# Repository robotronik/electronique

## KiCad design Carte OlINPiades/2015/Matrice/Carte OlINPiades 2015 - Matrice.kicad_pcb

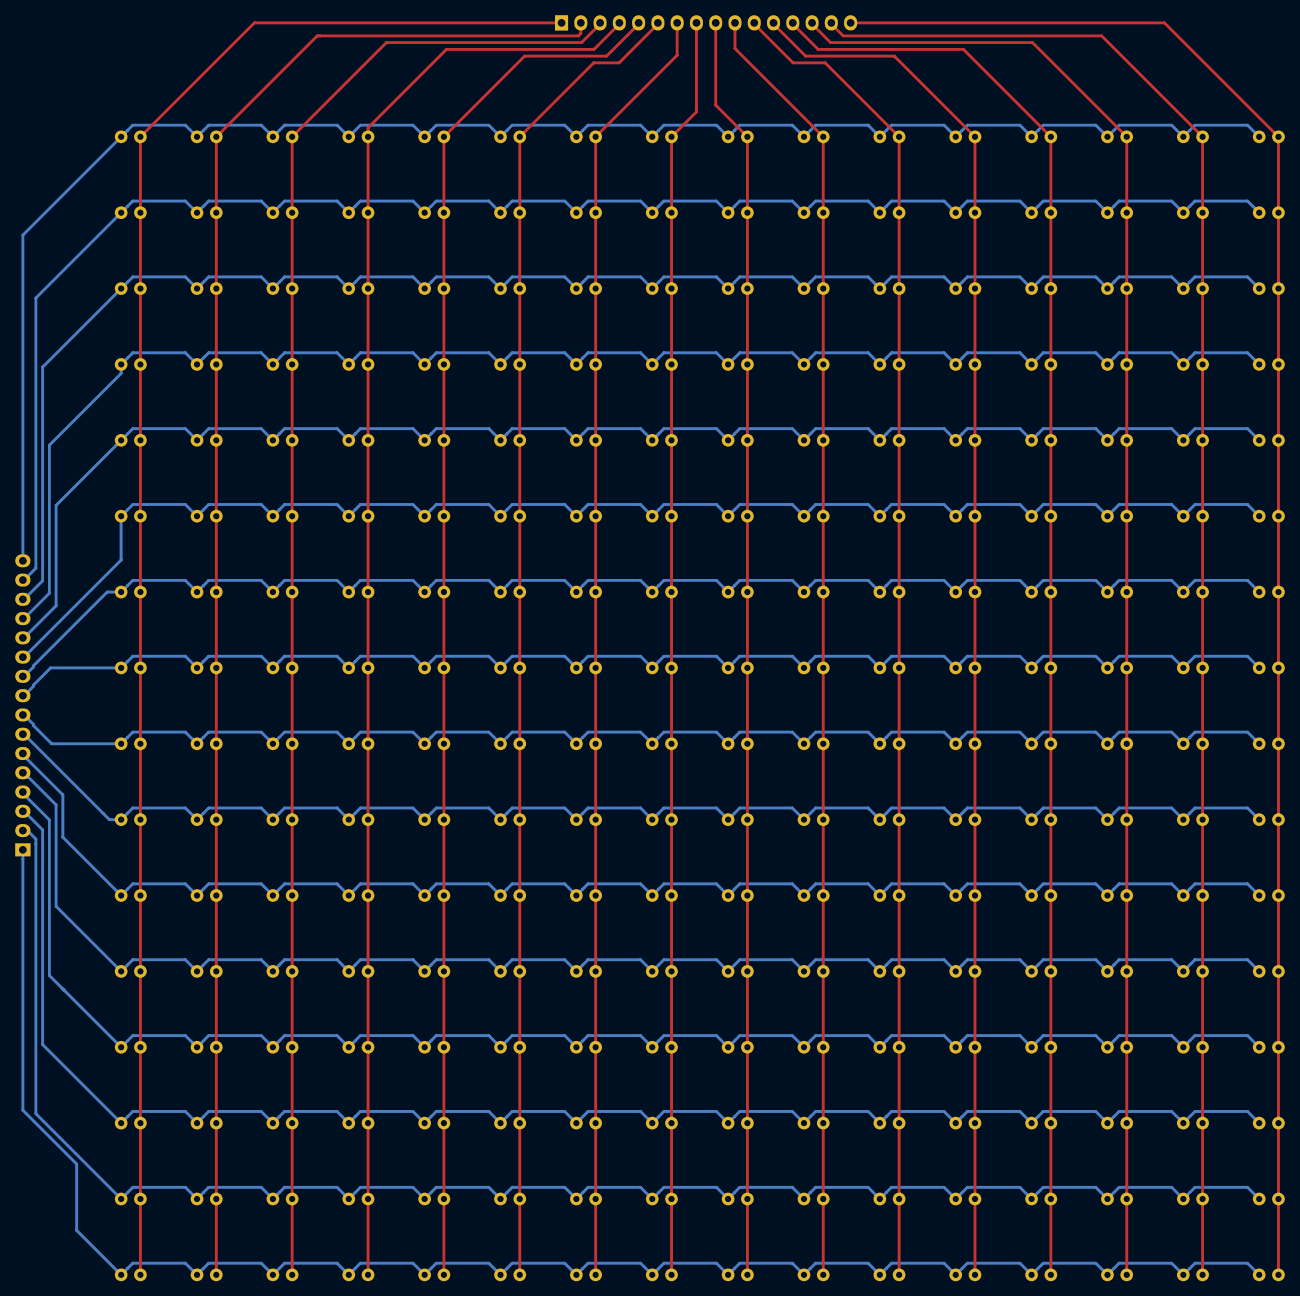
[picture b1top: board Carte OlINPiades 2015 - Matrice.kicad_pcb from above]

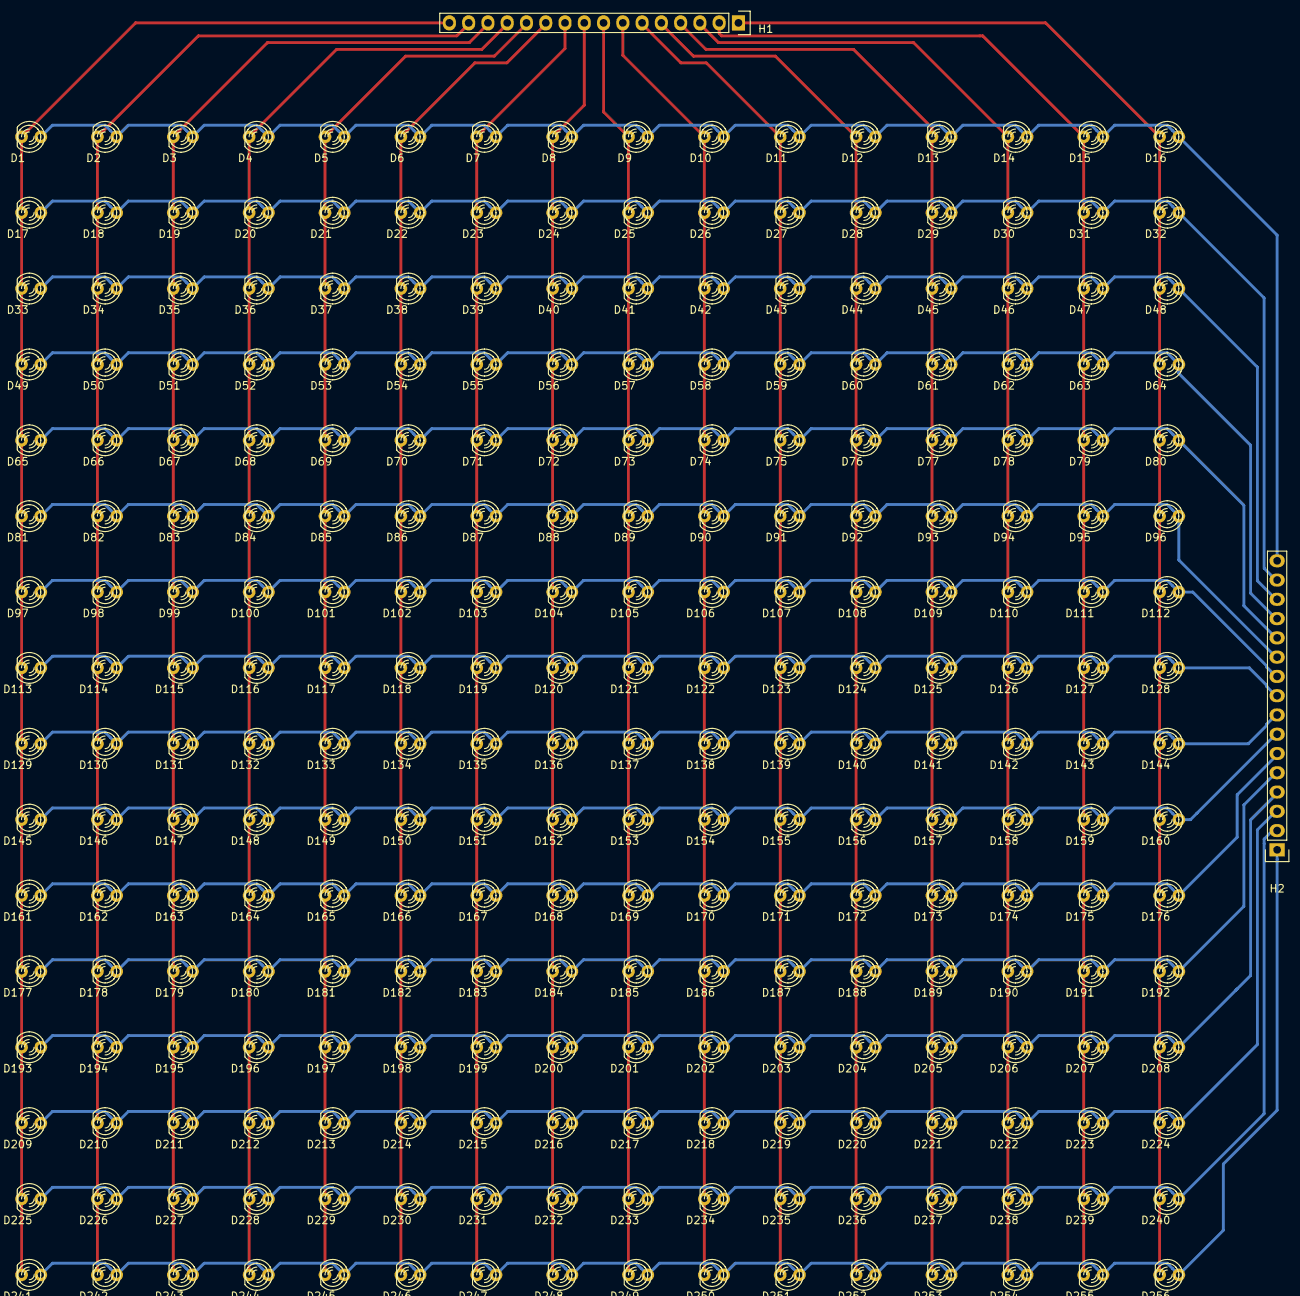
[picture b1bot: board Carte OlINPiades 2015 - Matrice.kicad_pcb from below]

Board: 2 copper layers, 258 parts (258 on the bottom side), 32 nets.

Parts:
D1, D2, D3, D4, D5, D6, D7, D8, D9, D10, D11, D12, D13, D14, D15, D16, D17, D18, D19, D20, D21, D22, D23, D24, D25, D26, D27, D28, D29, D30, D31, D32, D33, D34, D35, D36, D37, D38, D39, D40, D41, D42, D43, D44, D45, D46, D47, D48, D49, D50, D51, D52, D53, D54, D55, D56, D57, D58, D59, D60, D61, D62, D63, D64, D65, D66, D67, D68, D69, D70, D71, D72, D73, D74, D75, D76, D77, D78, D79, D80, D81, D82, D83, D84, D85, D86, D87, D88, D89, D90, D91, D92, D93, D94, D95, D96, D97, D98, D99, D100, D101, D102, D103, D104, D105, D106, D107, D108, D109, D110, D111, D112, D113, D114, D115, D116, D117, D118, D119, D120, D121, D122, D123, D124, D125, D126, D127, D128, D129, D130, D131, D132, D133, D134, D135, D136, D137, D138, D139, D140, D141, D142, D143, D144, D145, D146, D147, D148, D149, D150, D151, D152, D153, D154, D155, D156, D157, D158, D159, D160, D161, D162, D163, D164, D165, D166, D167, D168, D169, D170, D171, D172, D173, D174, D175, D176, D177, D178, D179, D180, D181, D182, D183, D184, D185, D186, D187, D188, D189, D190, D191, D192, D193, D194, D195, D196, D197, D198, D199, D200, D201, D202, D203, D204, D205, D206, D207, D208, D209, D210, D211, D212, D213, D214, D215, D216, D217, D218, D219, D220, D221, D222, D223, D224, D225, D226, D227, D228, D229, D230, D231, D232, D233, D234, D235, D236, D237, D238, D239, D240, D241, D242, D243, D244, D245, D246, D247, D248, D249, D250, D251, D252, D253, D254, D255, D256: LED; LED-3MM
H1, H2: PinHeader; Pin_Header_Straight_1x16

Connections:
unnamed: D1.1, D2.1, D3.1, D4.1, D5.1, D6.1, D7.1, D8.1, D9.1, D10.1, D11.1, D12.1, D13.1, D14.1, D15.1, D16.1, H2.16
unnamed: D1.2, D17.2, D33.2, D49.2, D65.2, D81.2, D97.2, D113.2, D129.2, D145.2, D161.2, D177.2, D193.2, D209.2, D225.2, D241.2, H1.16
unnamed: D10.2, D26.2, D42.2, D58.2, D74.2, D90.2, D106.2, D122.2, D138.2, D154.2, D170.2, D186.2, D202.2, D218.2, D234.2, D250.2, H1.7
unnamed: D17.1, D18.1, D19.1, D20.1, D21.1, D22.1, D23.1, D24.1, D25.1, D26.1, D27.1, D28.1, D29.1, D30.1, D31.1, D32.1, H2.15
unnamed: D33.1, D34.1, D35.1, D36.1, D37.1, D38.1, D39.1, D40.1, D41.1, D42.1, D43.1, D44.1, D45.1, D46.1, D47.1, D48.1, H2.14
unnamed: D49.1, D50.1, D51.1, D52.1, D53.1, D54.1, D55.1, D56.1, D57.1, D58.1, D59.1, D60.1, D61.1, D62.1, D63.1, D64.1, H2.13
unnamed: D65.1, D66.1, D67.1, D68.1, D69.1, D70.1, D71.1, D72.1, D73.1, D74.1, D75.1, D76.1, D77.1, D78.1, D79.1, D80.1, H2.12
unnamed: D81.1, D82.1, D83.1, D84.1, D85.1, D86.1, D87.1, D88.1, D89.1, D90.1, D91.1, D92.1, D93.1, D94.1, D95.1, D96.1, H2.11
unnamed: D97.1, D98.1, D99.1, D100.1, D101.1, D102.1, D103.1, D104.1, D105.1, D106.1, D107.1, D108.1, D109.1, D110.1, D111.1, D112.1, H2.10
unnamed: D4.2, D20.2, D36.2, D52.2, D68.2, D84.2, D100.2, D116.2, D132.2, D148.2, D164.2, D180.2, D196.2, D212.2, D228.2, D244.2, H1.13
unnamed: D5.2, D21.2, D37.2, D53.2, D69.2, D85.2, D101.2, D117.2, D133.2, D149.2, D165.2, D181.2, D197.2, D213.2, D229.2, D245.2, H1.12
unnamed: D6.2, D22.2, D38.2, D54.2, D70.2, D86.2, D102.2, D118.2, D134.2, D150.2, D166.2, D182.2, D198.2, D214.2, D230.2, D246.2, H1.11
unnamed: D7.2, D23.2, D39.2, D55.2, D71.2, D87.2, D103.2, D119.2, D135.2, D151.2, D167.2, D183.2, D199.2, D215.2, D231.2, D247.2, H1.10
unnamed: D8.2, D24.2, D40.2, D56.2, D72.2, D88.2, D104.2, D120.2, D136.2, D152.2, D168.2, D184.2, D200.2, D216.2, D232.2, D248.2, H1.9
unnamed: D9.2, D25.2, D41.2, D57.2, D73.2, D89.2, D105.2, D121.2, D137.2, D153.2, D169.2, D185.2, D201.2, D217.2, D233.2, D249.2, H1.8
unnamed: D11.2, D27.2, D43.2, D59.2, D75.2, D91.2, D107.2, D123.2, D139.2, D155.2, D171.2, D187.2, D203.2, D219.2, D235.2, D251.2, H1.6
unnamed: D12.2, D28.2, D44.2, D60.2, D76.2, D92.2, D108.2, D124.2, D140.2, D156.2, D172.2, D188.2, D204.2, D220.2, D236.2, D252.2, H1.5
unnamed: D13.2, D29.2, D45.2, D61.2, D77.2, D93.2, D109.2, D125.2, D141.2, D157.2, D173.2, D189.2, D205.2, D221.2, D237.2, D253.2, H1.4
unnamed: D14.2, D30.2, D46.2, D62.2, D78.2, D94.2, D110.2, D126.2, D142.2, D158.2, D174.2, D190.2, D206.2, D222.2, D238.2, D254.2, H1.3
unnamed: D15.2, D31.2, D47.2, D63.2, D79.2, D95.2, D111.2, D127.2, D143.2, D159.2, D175.2, D191.2, D207.2, D223.2, D239.2, D255.2, H1.2
unnamed: D16.2, D32.2, D48.2, D64.2, D80.2, D96.2, D112.2, D128.2, D144.2, D160.2, D176.2, D192.2, D208.2, D224.2, D240.2, D256.2, H1.1
unnamed: D113.1, D114.1, D115.1, D116.1, D117.1, D118.1, D119.1, D120.1, D121.1, D122.1, D123.1, D124.1, D125.1, D126.1, D127.1, D128.1, H2.9
unnamed: D2.2, D18.2, D34.2, D50.2, D66.2, D82.2, D98.2, D114.2, D130.2, D146.2, D162.2, D178.2, D194.2, D210.2, D226.2, D242.2, H1.15
unnamed: D3.2, D19.2, D35.2, D51.2, D67.2, D83.2, D99.2, D115.2, D131.2, D147.2, D163.2, D179.2, D195.2, D211.2, D227.2, D243.2, H1.14
unnamed: D129.1, D130.1, D131.1, D132.1, D133.1, D134.1, D135.1, D136.1, D137.1, D138.1, D139.1, D140.1, D141.1, D142.1, D143.1, D144.1, H2.8
unnamed: D145.1, D146.1, D147.1, D148.1, D149.1, D150.1, D151.1, D152.1, D153.1, D154.1, D155.1, D156.1, D157.1, D158.1, D159.1, D160.1, H2.7
unnamed: D161.1, D162.1, D163.1, D164.1, D165.1, D166.1, D167.1, D168.1, D169.1, D170.1, D171.1, D172.1, D173.1, D174.1, D175.1, D176.1, H2.6
unnamed: D177.1, D178.1, D179.1, D180.1, D181.1, D182.1, D183.1, D184.1, D185.1, D186.1, D187.1, D188.1, D189.1, D190.1, D191.1, D192.1, H2.5
unnamed: D193.1, D194.1, D195.1, D196.1, D197.1, D198.1, D199.1, D200.1, D201.1, D202.1, D203.1, D204.1, D205.1, D206.1, D207.1, D208.1, H2.4
unnamed: D209.1, D210.1, D211.1, D212.1, D213.1, D214.1, D215.1, D216.1, D217.1, D218.1, D219.1, D220.1, D221.1, D222.1, D223.1, D224.1, H2.3
unnamed: D225.1, D226.1, D227.1, D228.1, D229.1, D230.1, D231.1, D232.1, D233.1, D234.1, D235.1, D236.1, D237.1, D238.1, D239.1, D240.1, H2.2
unnamed: D241.1, D242.1, D243.1, D244.1, D245.1, D246.1, D247.1, D248.1, D249.1, D250.1, D251.1, D252.1, D253.1, D254.1, D255.1, D256.1, H2.1

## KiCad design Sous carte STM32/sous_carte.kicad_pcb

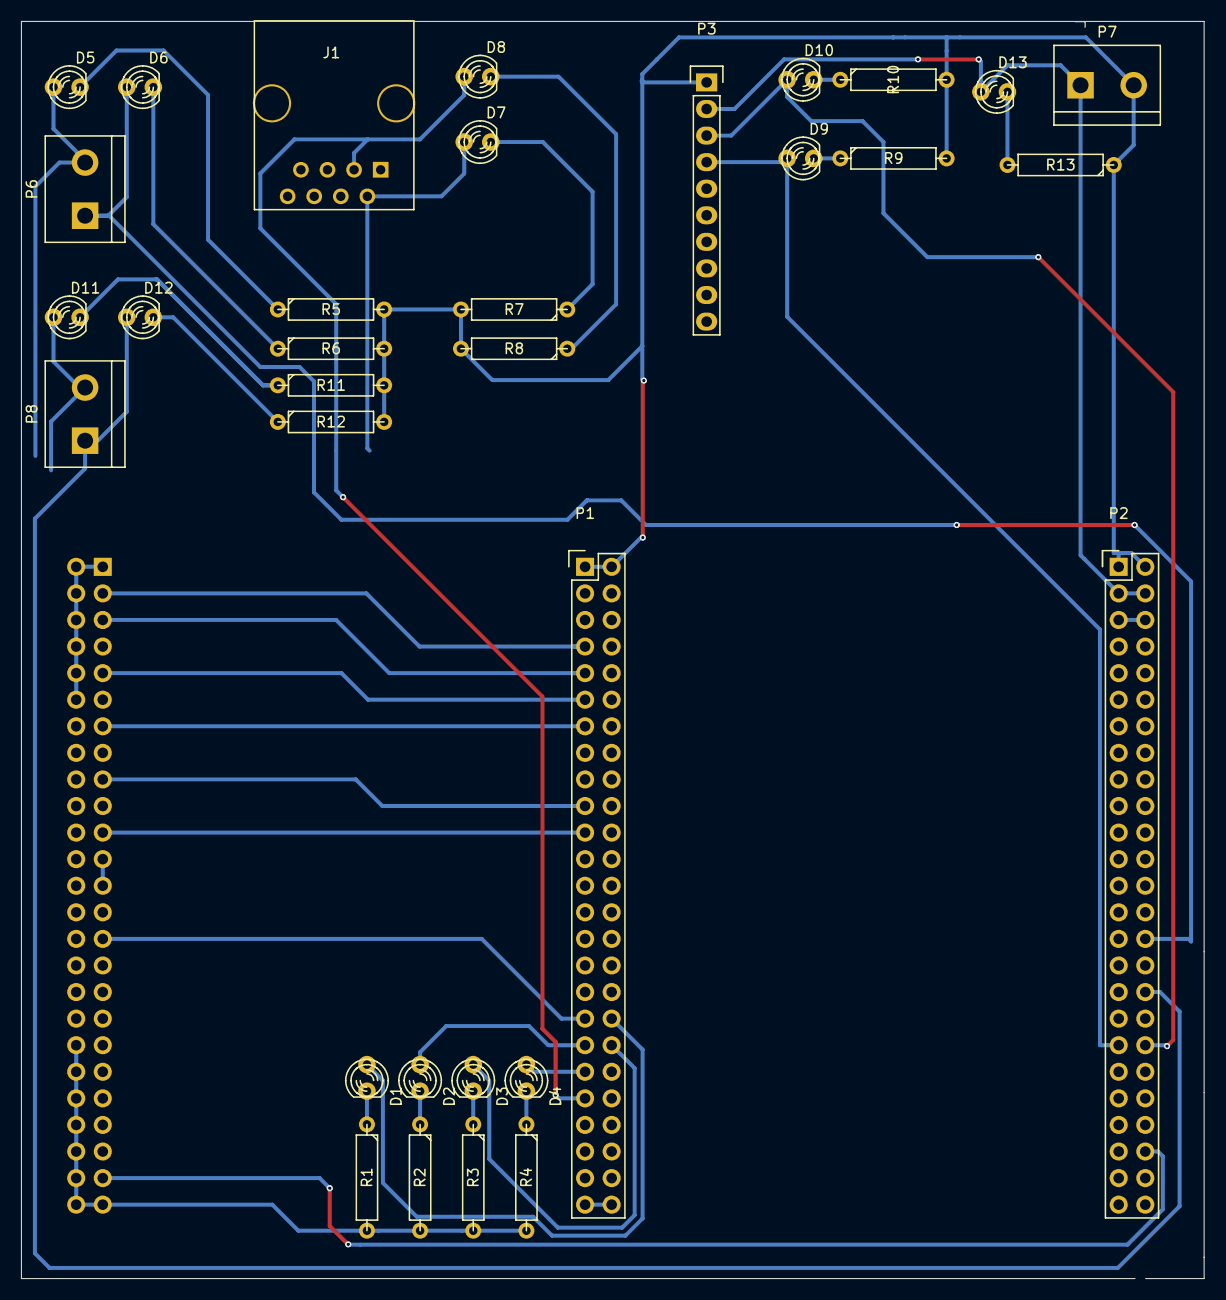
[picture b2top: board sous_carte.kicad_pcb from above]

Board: 2 copper layers, 113.0 x 120.1 mm, 34 parts (1 on the bottom side), 61 nets.

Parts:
D1, D2, D3, D4, D5, D6, D7, D8, D9, D10, D11, D12, D13: LED; LED-3MM
J1: RJ45; RJ45_8
P1, P2, P5: CONN_25X2; Pin_Header_Straight_2x25
P3: CONN_4; Pin_Header_Straight_1x10
P6, P7, P8: CONN_2; bornier2
R1, R2, R3, R4, R5, R6, R7, R8, R9, R10, R11, R12, R13: R; R4

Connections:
3V3: P2.5, P2.6
5V: D13.1, P2.3, P2.4, P3.2, P7.1
A0: P1.12, P5.11
A1: P1.11, P5.9
A2: P1.14, P5.15
A3: P1.13, P5.13
B1: P1.21, P5.21
B3: P2.28, P5.43
B4: P2.25, P5.39
B5: P2.26, P5.41
B6: P2.23, P5.35
B7: P2.24, P5.37
B8: P2.19, P5.31
B9: P2.20, P5.33
B10: P1.34, P5.27
B11: P1.35, P5.29
B12: D1.1, P1.36
B13: D2.1, P1.37
B14: D3.1, P1.38
B15: D4.1, P1.39
C1: P1.7, P5.3
C2: P1.10, P5.7
C3: P1.9, P5.5
C4: P1.20, P5.19
C5: P1.19, P5.17
C8: P2.45, P5.45
C9: P2.46, P5.47
C12: D11.1, P2.35, P8.2
D2: D12.1, P2.34, P8.1
D9: D8.1, J1.3, P1.41
E4: P2.13, P5.14
E5: P2.14, P5.16
E6: P2.11, P5.18
E7: P1.25, P5.20
E8: P1.26, P5.22
E9: P1.27, P5.24
E10: P1.28, P5.26
E11: P1.29, P5.28
E12: P1.30, P5.30
E13: P1.31, P5.32
E14: P1.32, P5.34
E15: P1.33, P5.36
GND: P1.1, P1.2, P1.5, P1.23, P1.49, P1.50, P2.1, P2.2, P2.49, P2.50, P3.1, P5.1, P5.2, P5.4, P5.6, P5.8, P5.10, P5.12, P5.23, P5.25, P5.38, P5.40, P5.42, P5.44, P5.46, P5.48, P5.49, P5.50, P7.2, R1.2, R2.2, R3.2, R4.2, R5.2, R6.2, R7.2, R8.2, R9.2, R10.2, R11.2, R12.2, R13.1
unnamed: D1.2, R1.1
unnamed: D2.2, R2.1
unnamed: D3.2, R3.1
unnamed: D4.2, R4.1
unnamed: D5.2, R5.1
unnamed: D6.2, R6.1
unnamed: D7.2, R7.1
unnamed: D8.2, R8.1
unnamed: D9.2, R9.1
unnamed: D10.2, R10.1
unnamed: D11.2, R11.1
unnamed: D12.2, R12.1
unnamed: D13.2, R13.2
UART2_RX: D6.1, P2.30, P6.1
UART2_TX: D5.1, P2.29, P6.2
UART3_TX: D7.1, J1.2, P1.40
UART4_RX: D10.1, P2.38, P3.3
UART4_TX: D9.1, P2.37, P3.4

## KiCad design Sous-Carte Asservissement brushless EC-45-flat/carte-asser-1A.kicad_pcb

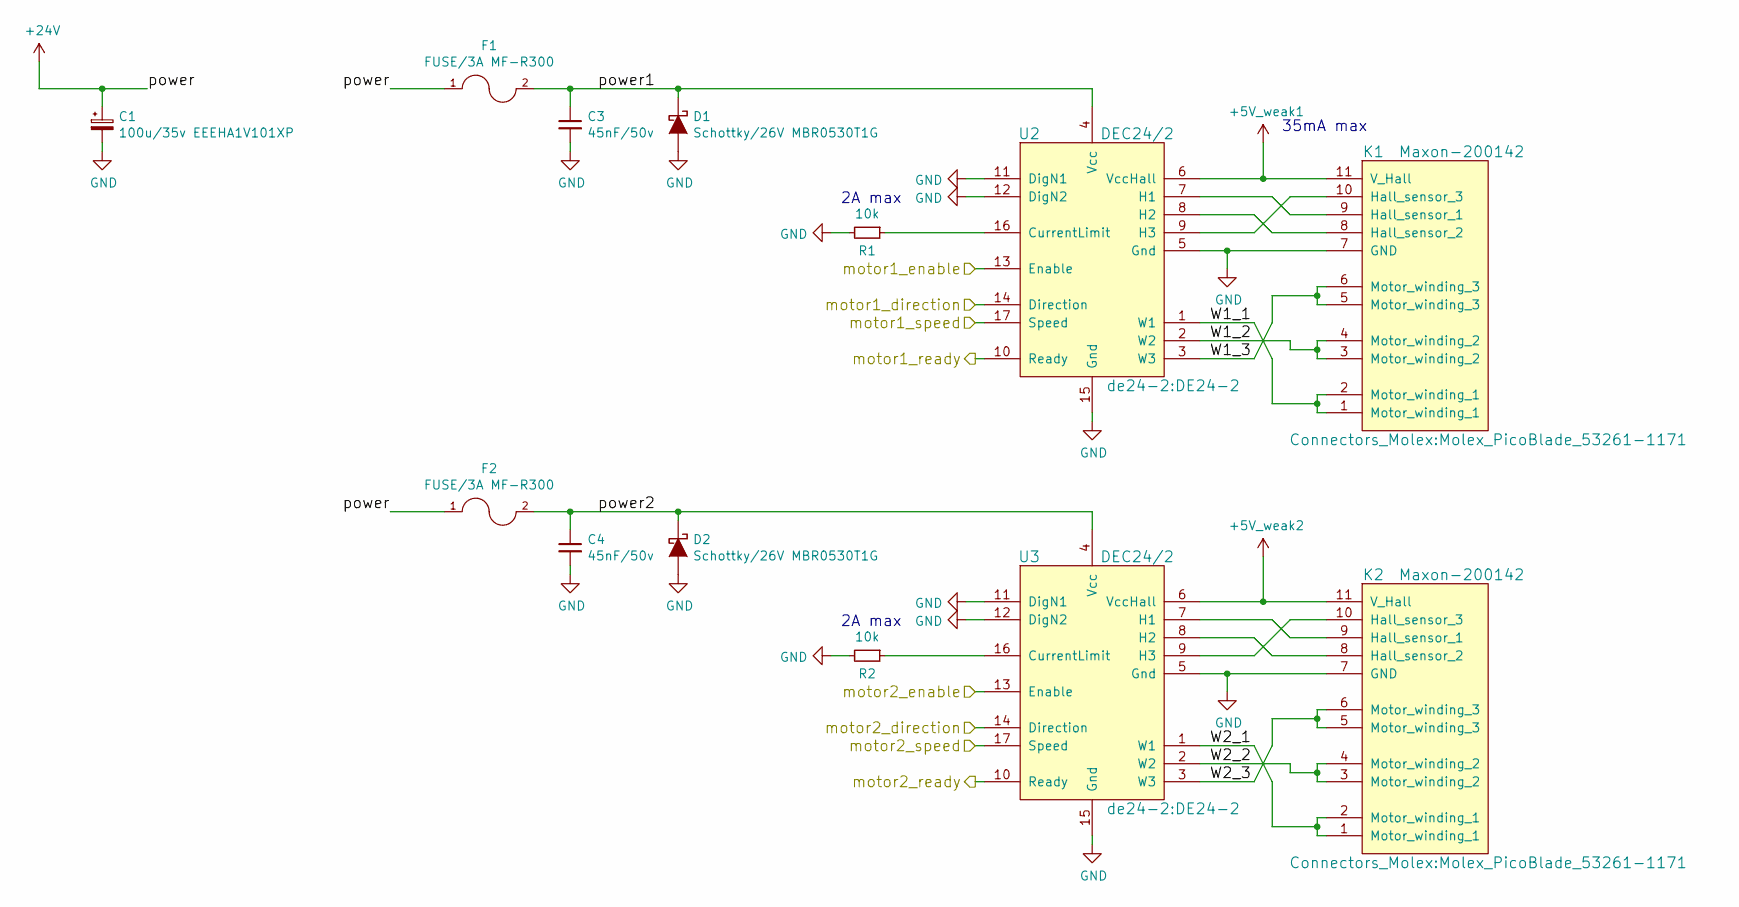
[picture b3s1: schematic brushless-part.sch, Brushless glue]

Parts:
C1: 100u/35v EEEHA1V101XP; c_elec_6.3x7.7
C3, C4: 45nF/50v; C_0805
D1, D2: Schottky/26V MBR0530T1G; SOD-123
F1, F2: FUSE/3A MF-R300; Fuse_TE5_Littlefuse-395Series
K1, K2: Maxon-200142; Molex_PicoBlade_53261-1171
R1, R2: 10k; R_0805
U2, U3: DEC24/2; DE24-2

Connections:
+5V_weak1: K1.11 (V_Hall), U2.6 (VccHall); also elsewhere on the board
+5V_weak2: K2.11 (V_Hall), U3.6 (VccHall); also elsewhere on the board
+24V: C1.1, F1.1, F2.1; also elsewhere on the board
/brushless-part/W1_1: K1.1 (Motor_winding_1), K1.2 (Motor_winding_1), U2.1 (W1)
/brushless-part/W1_2: K1.3 (Motor_winding_2), K1.4 (Motor_winding_2), U2.2 (W2)
/brushless-part/W1_3: K1.5 (Motor_winding_3), K1.6 (Motor_winding_3), U2.3 (W3)
/brushless-part/W2_1: K2.1 (Motor_winding_1), K2.2 (Motor_winding_1), U3.1 (W1)
/brushless-part/W2_2: K2.3 (Motor_winding_2), K2.4 (Motor_winding_2), U3.2 (W2)
/brushless-part/W2_3: K2.5 (Motor_winding_3), K2.6 (Motor_winding_3), U3.3 (W3)
/brushless-part/motor1_speed: U2.17 (Speed); also elsewhere on the board
/brushless-part/motor2_speed: U3.17 (Speed); also elsewhere on the board
/brushless-part/power1: C3.1, D1.1 (K), F1.2, U2.4 (Vcc)
/brushless-part/power2: C4.1, D2.1 (K), F2.2, U3.4 (Vcc)
/uC-part/gpio_direction1: U2.14 (Direction); also elsewhere on the board
/uC-part/gpio_direction2: U3.14 (Direction); also elsewhere on the board
/uC-part/gpio_enable: U2.13 (Enable), U3.13 (Enable); also elsewhere on the board
/uC-part/gpio_ready1: U2.10 (Ready); also elsewhere on the board
/uC-part/gpio_ready2: U3.10 (Ready); also elsewhere on the board
GND: C1.2, C3.2, C4.2, D1.2 (A), D2.2 (A), K1.7 (GND), K2.7 (GND), R1.2, R2.2, U2.5 (Gnd), U2.11 (DigN1), U2.12 (DigN2), U2.15 (Gnd), U3.5 (Gnd), U3.11 (DigN1), U3.12 (DigN2), U3.15 (Gnd); also elsewhere on the board
unnamed: K1.8 (Hall_sensor_2), U2.8 (H2)
unnamed: K1.9 (Hall_sensor_1), U2.7 (H1)
unnamed: K1.10 (Hall_sensor_3), U2.9 (H3)
unnamed: K2.8 (Hall_sensor_2), U3.8 (H2)
unnamed: K2.9 (Hall_sensor_1), U3.7 (H1)
unnamed: K2.10 (Hall_sensor_3), U3.9 (H3)
unnamed: R1.1, U2.16 (CurrentLimit)
unnamed: R2.1, U3.16 (CurrentLimit)

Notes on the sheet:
2A max
35mA max

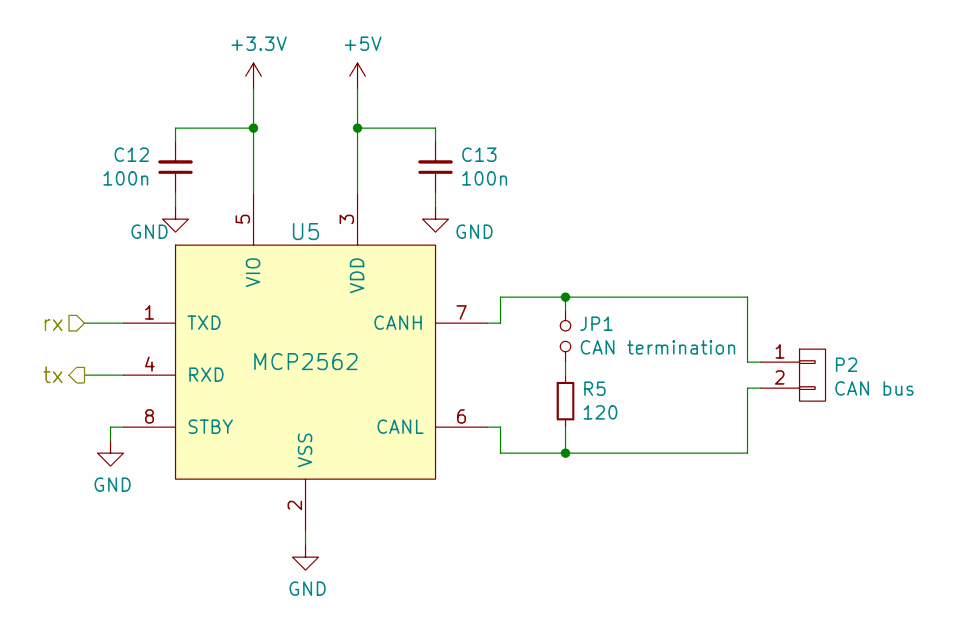
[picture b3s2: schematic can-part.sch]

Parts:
C12, C13: 100n; C_0805
JP1: CAN termination; Pin_Header_Straight_1x02
P2: CAN bus; Pin_Header_Straight_1x02
R5: 120; R_0805
U5: MCP2562; SOIC-8_3.9x4.9mm_Pitch1.27mm

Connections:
+3V3: C12.2, U5.5 (VIO); also elsewhere on the board
+5V: C13.2, U5.3 (VDD); also elsewhere on the board
/uC-part/can_rx: U5.4 (RXD); also elsewhere on the board
/uC-part/can_tx: U5.1 (TXD); also elsewhere on the board
GND: C12.1, C13.1, U5.2 (VSS), U5.8 (STBY); also elsewhere on the board
unnamed: JP1.1, P2.1, U5.7 (CANH)
unnamed: JP1.2, R5.1
unnamed: P2.2, R5.2, U5.6 (CANL)

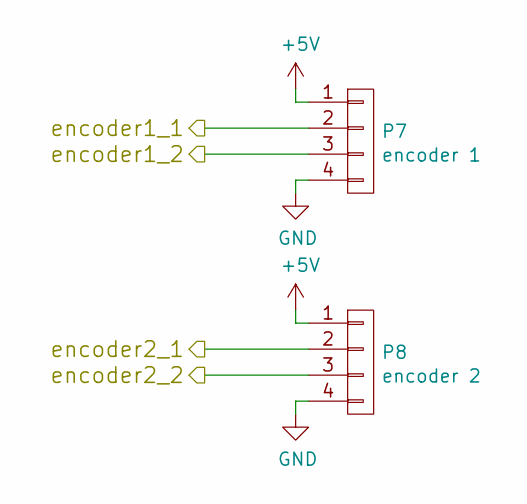
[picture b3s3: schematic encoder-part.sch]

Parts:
P7: encoder 1; Socket_Strip_Straight_1x04
P8: encoder 2; Socket_Strip_Straight_1x04

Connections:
+5V: P7.1, P8.1; also elsewhere on the board
/encoder-part/encoder1_1: P7.2; also elsewhere on the board
/encoder-part/encoder1_2: P7.3; also elsewhere on the board
/encoder-part/encoder2_1: P8.2; also elsewhere on the board
/encoder-part/encoder2_2: P8.3; also elsewhere on the board
GND: P7.4, P8.4; also elsewhere on the board

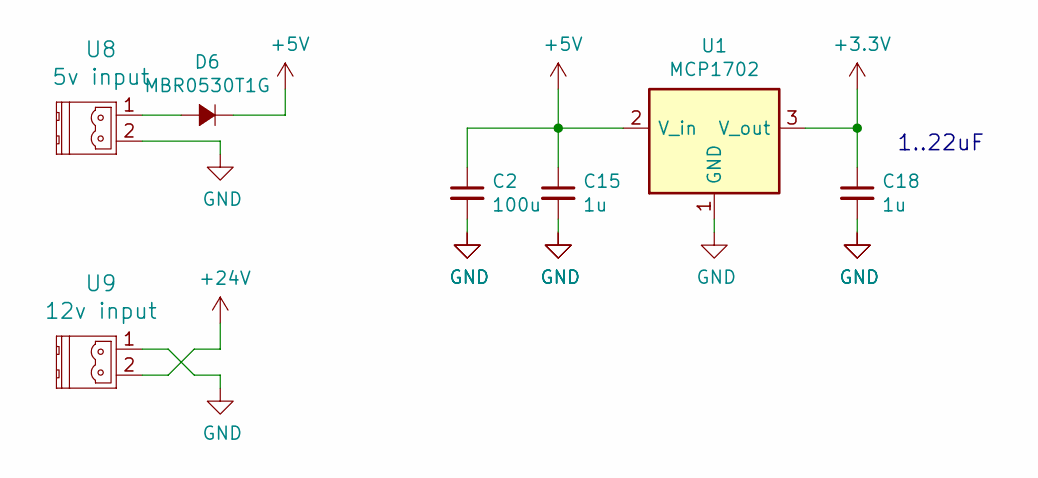
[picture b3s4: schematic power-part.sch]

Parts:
C2: 100u; c_elec_6.3x4.5
C15, C18: 1u; C_0805
D6: MBR0530T1G; SOD-123
U1: MCP1702; SOT89-3_Housing
U8: 5v input; B-plug-5mm
U9: 12v input; B-plug-5mm

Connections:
+3V3: C18.1, U1.3 (V_out); also elsewhere on the board
+5V: C2.1, C15.1, D6.1 (K), U1.2 (V_in); also elsewhere on the board
+24V: U9.2; also elsewhere on the board
GND: C2.2, C15.2, C18.2, U1.1 (GND), U8.2, U9.1; also elsewhere on the board
unnamed: D6.2 (A), U8.1

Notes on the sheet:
1..22uF

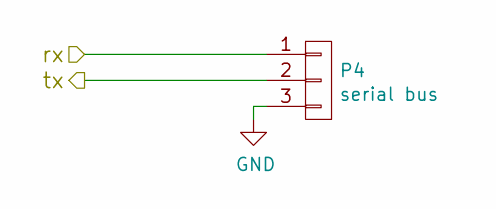
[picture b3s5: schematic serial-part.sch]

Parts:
P4: serial bus; Socket_Strip_Straight_1x03

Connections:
/serial-part/rx: P4.1; also elsewhere on the board
/serial-part/tx: P4.2; also elsewhere on the board
GND: P4.3; also elsewhere on the board

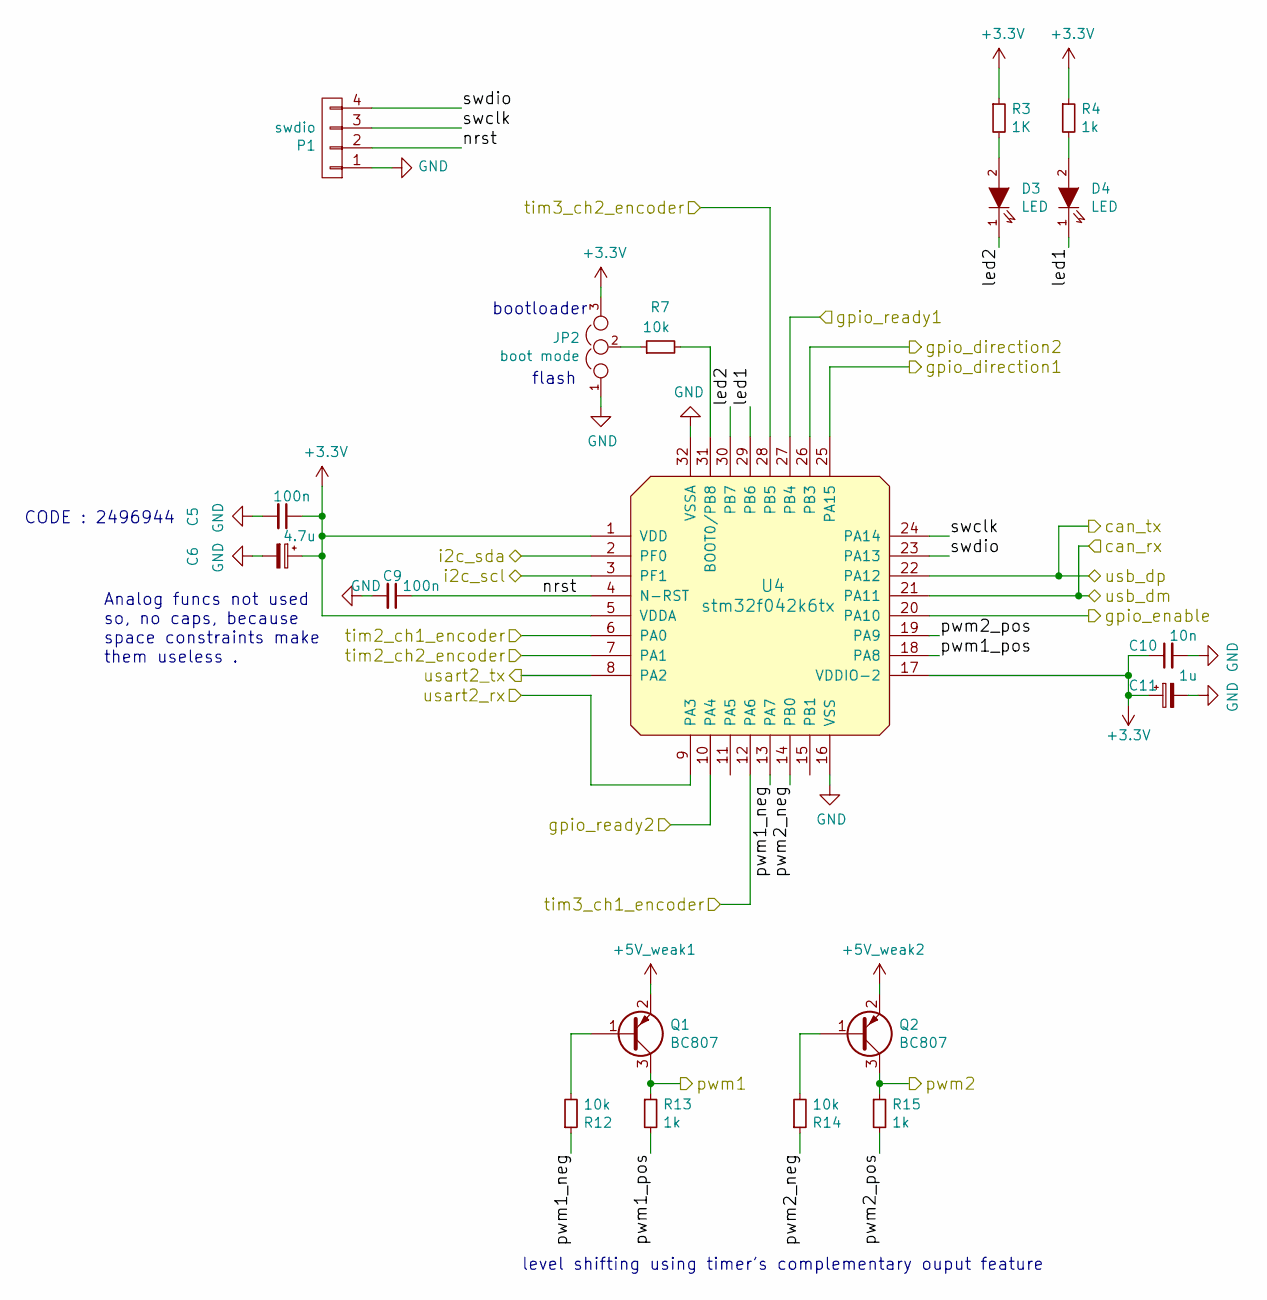
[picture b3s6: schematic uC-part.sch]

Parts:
C5, C9: 100n; C_0805
C6: 4.7u; C_0805
C10: 10n; C_0805
C11: 1u; C_0805
D3, D4: LED; LED_0805
JP2: boot mode; jumper_switch_3
P1: swdio; Pin_Header_Straight_1x04
Q1, Q2: BC807; SOT-23
R3: 1K; R_0805
R4, R13, R15: 1k; R_0805
R7, R12, R14: 10k; R_0805
U4: stm32f042k6tx; LQFP-32_7x7mm_Pitch0.8mm

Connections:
+3V3: C5.1, C6.1, C10.1, C11.1, JP2.3, R3.1, R4.1, U4.1 (VDD), U4.5 (VDDA), U4.17 (VDDIO-2); also elsewhere on the board
+5V_weak1: Q1.2 (E); also elsewhere on the board
+5V_weak2: Q2.2 (E); also elsewhere on the board
/brushless-part/motor1_speed: Q1.3 (C), R13.1; also elsewhere on the board
/brushless-part/motor2_speed: Q2.3 (C), R15.1; also elsewhere on the board
/encoder-part/encoder1_1: U4.6 (PA0); also elsewhere on the board
/encoder-part/encoder1_2: U4.7 (PA1); also elsewhere on the board
/encoder-part/encoder2_1: U4.12 (PA6); also elsewhere on the board
/encoder-part/encoder2_2: U4.28 (PB5); also elsewhere on the board
/serial-part/rx: U4.8 (PA2); also elsewhere on the board
/serial-part/tx: U4.9 (PA3); also elsewhere on the board
/uC-part/can_rx: U4.21 (PA11); also elsewhere on the board
/uC-part/can_tx: U4.22 (PA12); also elsewhere on the board
/uC-part/gpio_direction1: U4.25 (PA15); also elsewhere on the board
/uC-part/gpio_direction2: U4.26 (PB3); also elsewhere on the board
/uC-part/gpio_enable: U4.20 (PA10); also elsewhere on the board
/uC-part/gpio_ready1: U4.27 (PB4); also elsewhere on the board
/uC-part/gpio_ready2: U4.10 (PA4); also elsewhere on the board
/uC-part/i2c_scl: U4.3 (PF1); also elsewhere on the board
/uC-part/i2c_sda: U4.2 (PF0); also elsewhere on the board
/uC-part/led1: D4.1 (K), U4.29 (PB6)
/uC-part/led2: D3.1 (K), U4.30 (PB7)
/uC-part/nrst: C9.1, P1.2, U4.4 (N-RST)
/uC-part/pwm1_neg: R12.1, U4.13 (PA7)
/uC-part/pwm1_pos: R13.2, U4.18 (PA8)
/uC-part/pwm2_neg: R14.1, U4.14 (PB0)
/uC-part/pwm2_pos: R15.2, U4.19 (PA9)
/uC-part/swclk: P1.3, U4.24 (PA14)
/uC-part/swdio: P1.4, U4.23 (PA13)
GND: C5.2, C6.2, C9.2, C10.2, C11.2, JP2.1, P1.1, U4.16 (VSS), U4.32 (VSSA); also elsewhere on the board
unnamed: D3.2 (A), R3.2
unnamed: D4.2 (A), R4.2
unnamed: JP2.2, R7.1
unnamed: Q1.1 (B), R12.2
unnamed: Q2.1 (B), R14.2
unnamed: R7.2, U4.31 (BOOT0/PB8)

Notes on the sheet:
flash
bootloader
level shifting using timer's complementary ouput feature
CODE : 2496944
Analog funcs not used so, no caps, because space constraints make them useless .

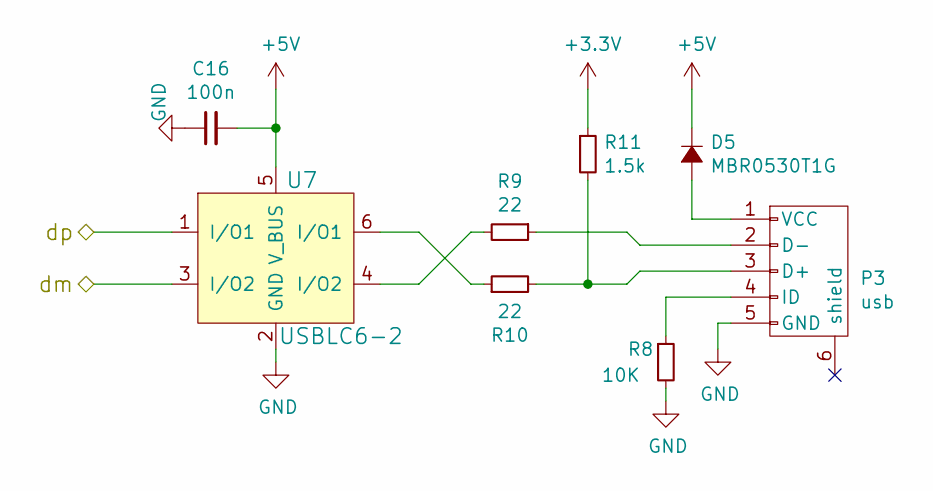
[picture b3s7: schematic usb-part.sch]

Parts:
C16: 100n; C_0805
D5: MBR0530T1G; SOD-123
P3: usb; USB_Mini-B
R8: 10K; R_0805
R9, R10: 22; R_0805
R11: 1.5k; R_0805
U7: USBLC6-2; SOT-23-6

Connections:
+3V3: R11.1; also elsewhere on the board
+5V: C16.2, D5.1 (K), U7.5 (V_BUS); also elsewhere on the board
/uC-part/can_rx: U7.3 (I/O2); also elsewhere on the board
/uC-part/can_tx: U7.1 (I/O1); also elsewhere on the board
GND: C16.1, P3.5 (GND), R8.2, U7.2 (GND); also elsewhere on the board
unnamed: D5.2 (A), P3.1 (VCC)
unnamed: P3.2 (D-), R9.1
unnamed: P3.3 (D+), R10.2, R11.2
unnamed: P3.4 (ID), R8.1
unnamed: R9.2, U7.4 (I/O2)
unnamed: R10.1, U7.6 (I/O1)

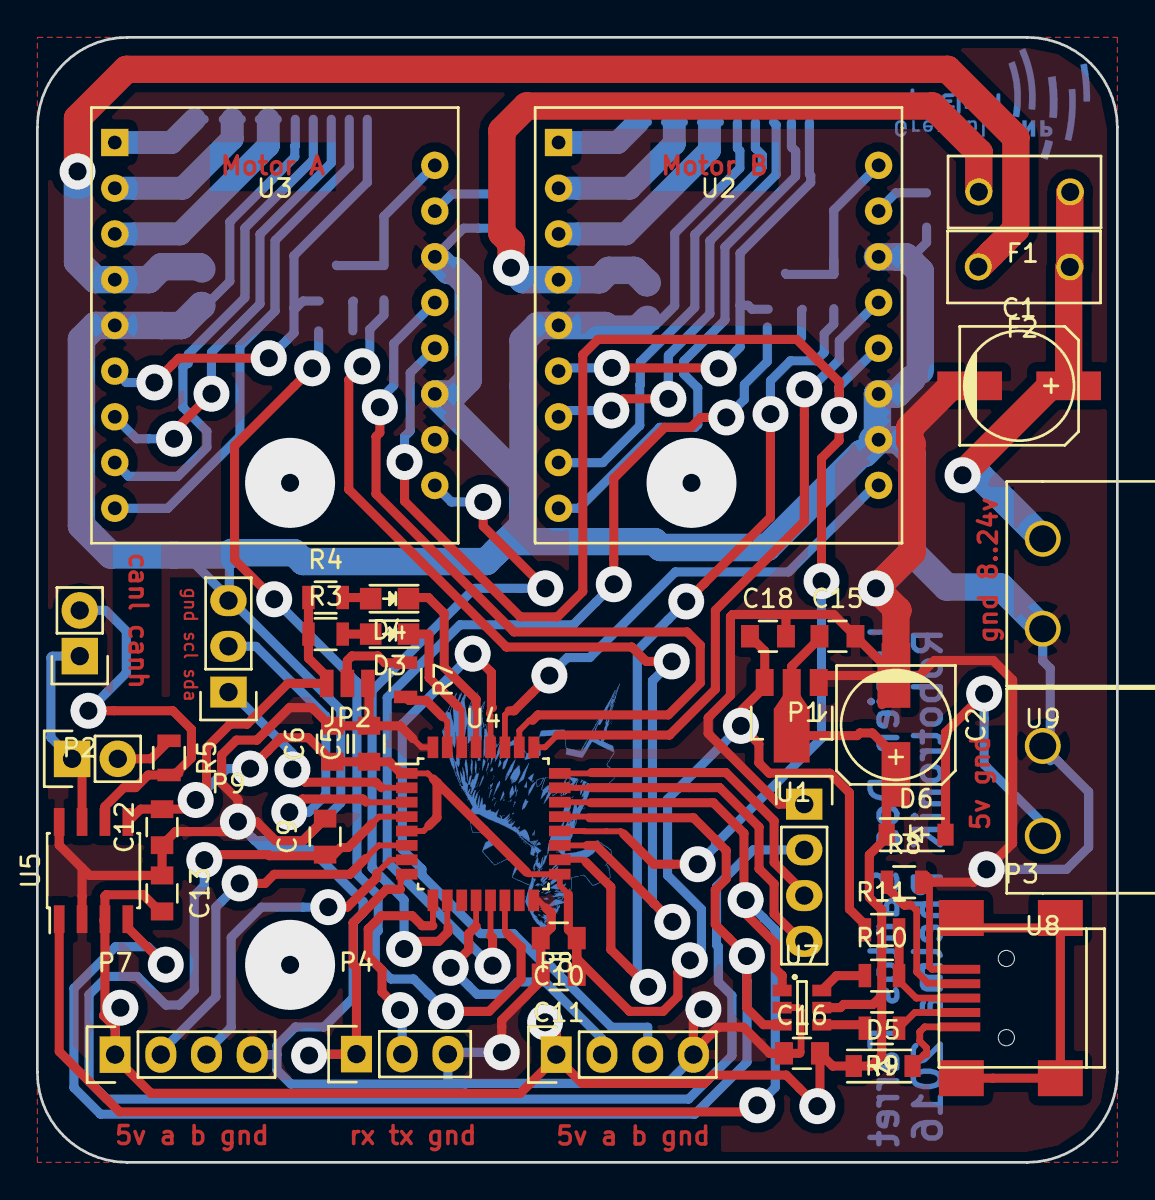
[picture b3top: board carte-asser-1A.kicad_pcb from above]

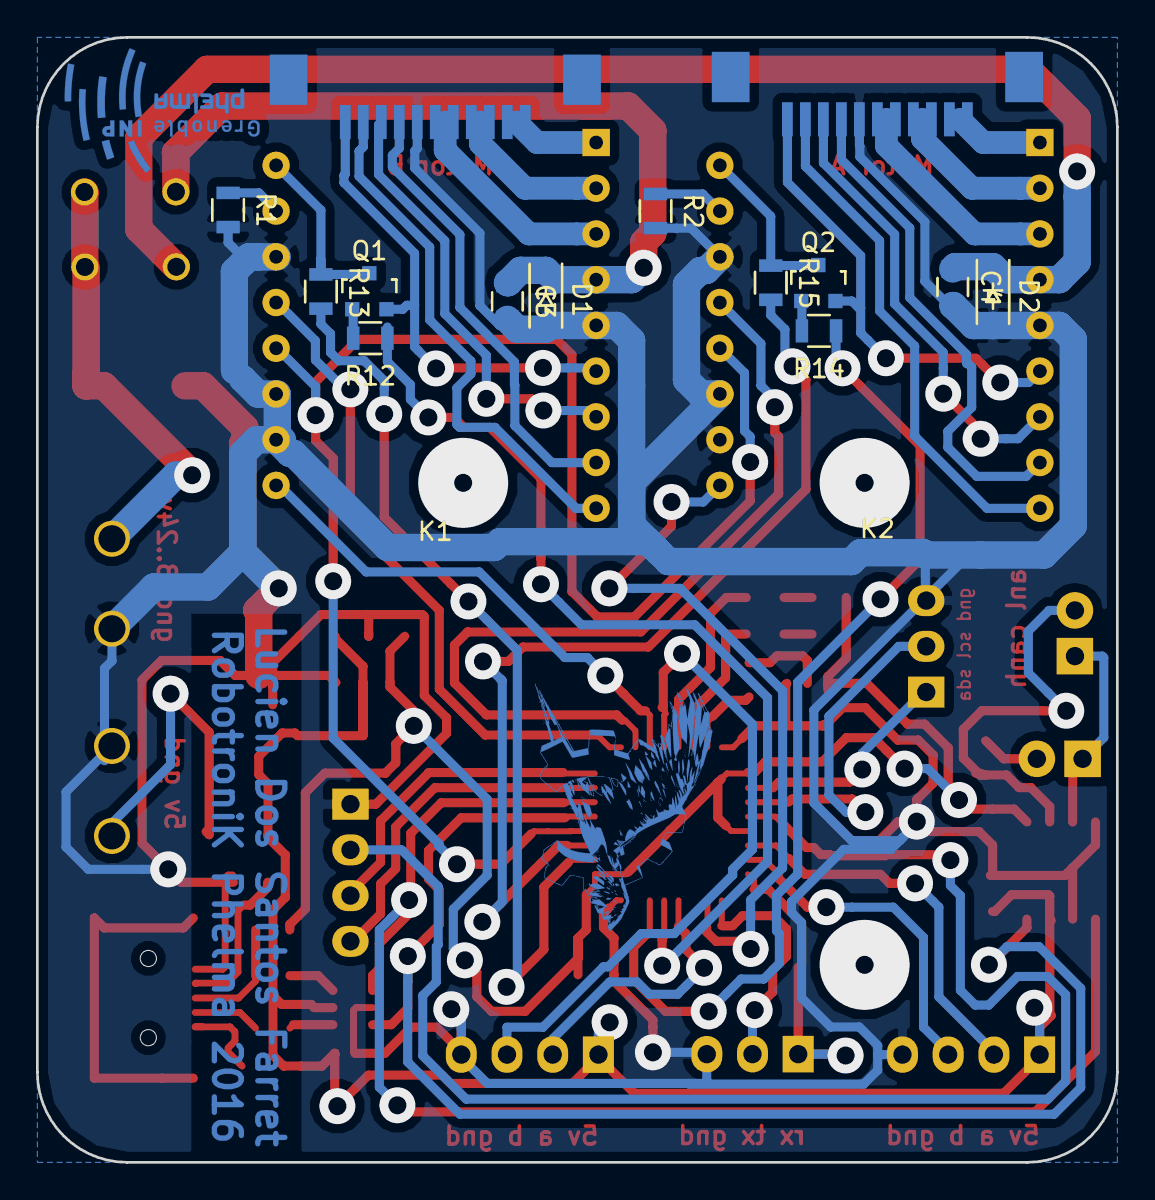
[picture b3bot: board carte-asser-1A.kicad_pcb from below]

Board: 2 copper layers, 60.0 x 62.5 mm, 57 parts (14 on the bottom side), 64 nets.

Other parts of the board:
P9: i2c bus; Pin_Header_Straight_1x03

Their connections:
/uC-part/i2c_scl: P9.2; also elsewhere on the board
/uC-part/i2c_sda: P9.1; also elsewhere on the board
GND: P9.3; also elsewhere on the board

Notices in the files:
carte_2015/.kicad_pcb.kicad_pcb:
Robotronik© 2014
